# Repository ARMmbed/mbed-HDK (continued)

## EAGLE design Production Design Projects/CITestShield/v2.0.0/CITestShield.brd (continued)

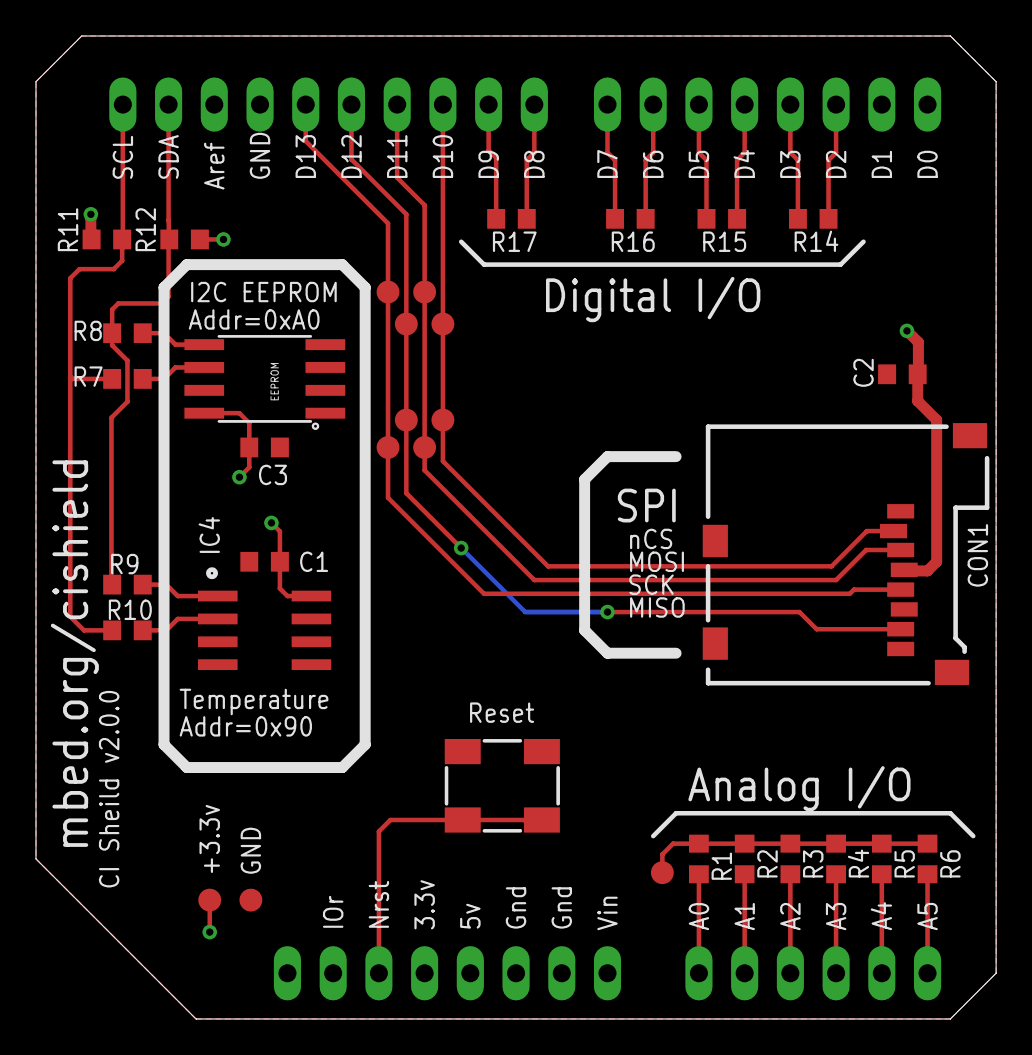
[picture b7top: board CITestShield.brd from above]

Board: 2 copper layers, 53.3 x 54.6 mm, 35 parts (0 on the bottom side), 28 nets.

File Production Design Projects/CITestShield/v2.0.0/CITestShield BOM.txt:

Qty Value              Device             Package                 Parts                                                   
8   0R                 R0603              0603                    R7, R8, R9, R10, R14, R15, R16, R17                                        
3   100nF              C0603              0603                    C1, C2, C3                                              
6   10k                R0603              0603                    R1, R2, R3, R4, R5, R6                                                          
2   4k7                R0603              0603                    R11, R12                                                                        
1   AT24LCXXXEIAJ      AT24LCXXXEIAJ      SO08-EIAJ               EEPROM                                                   
1   LM75BD             LM75BD             SO8                     IC4                                                                             
1   MICRO-SD           MICRO-SD           AMPHENOL-101-00660-68-6 CON1                                                                            
1   SPST-4_TP1154_J    SPST-4_TP1154_J    TP-1154X                SW1

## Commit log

2016-07-27 Initial import of mbed HDK
    This is based on the hg repository that was hosted on
    developer.mbed.org - it includes some of the same projects but also
    adds the mbed 6LoWPAN Boarder Router Hat.
2016-07-27 Migrate Handbook page to Readme.md
    Removed section on 'where to find the HDK' as that's
    the repository that the Readme is describing.
2016-08-26 Updated 6LoWPAN Border Router HDK to Rev 1.1
2016-08-26 Rev 1.1 for 6LoWPAN Border Router Hat
2016-08-26 Update Gerbers
2016-08-30 Cleaned Schematic
2016-09-02 Cleaned up silk screen
2016-09-05 Updated sch and brd for final build
2016-09-05 Added all output CAM files V_1_1
2016-09-05 Final version V_1_1 of Border Router Hat Job
2016-09-05 Updated ignore files
2016-09-05 Rev 1.1 for 6LoWPAN Border Router Hat
    Update Gerbers
    Cleaned Schematic
    Cleaned up silk screen
    Updated sch and brd for final build
    Added all output CAM files V_1_1
    Final version V_1_1 of Border Router Hat Job
2016-09-06 Restructure
2016-09-08 Creating the index file
    This is to publish on docs.mbed without removing or duplicating the readme you have in the root directory
2016-09-08 Creating the YML file
    This is to publish on docs.mbed
2016-09-16 Updated Docs
2016-09-19 Added CI Test Shield Production Design
2016-09-23 Adding the link
    Since we need it from docs.mbed
2016-09-27 Removed outdated schematic
2016-09-27 removed obsolete silkscreen on hidden layers that showed up on OSHParks rendering system
2016-09-27 adding BOM
2016-09-28 added readme with links to software, ebom, and pcb
2016-10-24 Added Readme for each design
2016-10-27 Updated readmes, incldued eBOMs, included images
2016-11-04 Updated Readme error
2016-11-04 Made presentation and links clearer Readme
2016-11-04 Release of v2.0.0 CI test shield, removal of R13(UART Tests Removed)
2016-11-10 Updated SilkScreen Layers
2016-11-10 Updated Readme Image
2016-11-10 Started work on new lib system
2016-11-11 Added Descriptions to Transistors
2016-11-14 Updating to new table format
2016-11-15 Completed transistor lin
2016-11-16 Completed All USB parts
2016-11-18 Designed Realtek Ameba DEV01 shield
2016-11-21 Added Multitech dragonfly breakout to library, added hirose 40 pin connector to library
2016-11-21 Corrections to connect lbr
2016-11-23 Added new SPST switch EVQ-P7A01P
2016-11-23 corrected issue
2016-11-24 Added 2 new power items
2016-11-24 Added ferrite bead
2016-11-24 updated lbr
2016-11-28 Update README.md
    Corrected typos.
2017-01-09 Updated all library parts, new structure
2017-01-09 Cleaned update
2017-01-10 Created Multitech xDOT LORA module footprint
2017-01-10 Updated prefix value for IC to U
2017-01-10 Updated ignore
2017-01-11 Added Multitech xDOT component
2017-01-11 Added 595-TLV73333PDBVT 300mA LDO
2017-01-11 Added xDOT as a reference Bare Design Project
2017-01-12 Added Ultra low profile switch, ammended Con and Power libraries
2017-01-13 Corrected Prefix
2017-01-19 Updated attributes
2017-01-30 Added STM32F429ZI LQFP-144 Device, updated all other packages to 0.04/12% vector silkscreen
2017-01-30 Updated STM32F429ZI
2017-02-23 Fixed Silkscreen missing 'DigitalIO'
2017-03-03 Updating and adding new components of LAIRD and UBLOX
2017-03-03 Updated descriptions
2017-03-03 Added TLV1117LV33DCYR 3.3V 1A REG
2017-03-20 House Keeping
2017-03-21 Added LPC1768 schematic PDF
2017-04-06 Updated libs
2017-04-12 Amended stm1061n IC voltage detector parts, pins of VSS and OUT were swapped
2017-05-07 Initial Import of mbedXdot Shield
2017-05-07 Added k64f/k22f based shield board
2017-05-07 Amended hidden text
2017-05-09 Added v1.0.0 BOM for NA and EU
2017-05-09 Amended pages in xDOT mbed shield design
2017-05-09 Final release of V1.0.0
2017-05-09 Added micro DPDT switch
2017-05-16 Change part to D6 to BAT60J
2017-05-18 Updated files to HDK-Contribute Guidlines
2017-05-23 Updated folder structure
2017-05-24 Removed DNP from mnt/mnb pick and place files
2017-06-01 initial hardware commit of v.1.1.0
2017-06-01 Added v1.1.0 updated schematic. R3:1.5K->220R, R13,R14:470R->1.5K, rerouted UART1_, moved USB micro into board, placed resistors R14-to-R27 on front of PCB (no components on rear)
2017-06-02 Updated file structure, added xlsx BOM
2017-06-02 Updated files names to match spec
2017-06-02 Updated file to spec
2017-06-02 Removed obsolete file
2017-06-05 Seperated Oscillator to seperate library, added actual parts for individual oscillators to help with BOM generation
2017-06-05 Removed ZIP file
2017-06-05 Updated readme to update changes in designs added
2017-06-05 Moved Crystal/Oscillator to own libr
2017-06-07 Added LPC11u35 interface macro
2017-06-07 Updated error
2017-06-08 Added PDF of SCH
2017-06-09 Added v1.1.0, see readme
2017-06-12 Added new oscillator
2017-06-12 Added new bare interface MK20DX128VFM5
2017-06-12 Updated schematic
2017-06-22 Updated BOM errors, updated file name errors
2017-06-23 In brief: mbed enabled SS logo, Battery Voltage via JST connector now 4.5V. See readme.md for more details
2017-06-23 Updated to 1.2.0
2017-06-23 Updated pick and place files
2017-06-23 Removed error
2017-06-23 fixed typo
2017-06-23 fixed typo in date
2017-07-05 Added ST DAPlink, untested
2017-07-05 Fixed PDF and name errors
2017-07-05 Added ST F1
2017-07-05 Added new parts
2017-07-05 Corrected
2017-07-06 Updated design removed obsolete components
2017-07-07 Added cortex headers
2017-07-07 Updated silkscreen
2017-07-10 Added new SPI flash
2017-07-10 Added SWD connectors
2017-07-14 Updated directory
2017-07-14 First add of guides
2017-07-14 Updated for new guides
2017-07-14 Update README.md
    Format error
2017-07-14 Update CONTRIBUTORS-GUIDE.md
    Amended link
2017-07-14 corrected name
2017-07-14 Amended
2017-08-08 Added LCD screen
2017-08-08 Added new sensors
2017-08-25 Updated parts
2017-08-25 ADDED LCD
2017-08-29 Updated symbols
2017-09-01 removed error in qfn-16 power ic package
2017-09-02 Removed error from switch package
2017-09-02 Updated package vector font
2017-09-15 New designs
2017-10-04 Production commit
2017-10-19 updated libaraies
2017-10-20 Updated vias on antenna from floting to ground, improve antenna performance
2017-10-20 Improved antenna performance moved single lines
2017-10-31 Corrected package size
2017-11-22 Changed incorrect MFN
2018-01-05 Added updated
2018-01-25 Added new components
2018-06-19 New IC
2018-09-17 Update README.md
    Add obsolete note to README.
